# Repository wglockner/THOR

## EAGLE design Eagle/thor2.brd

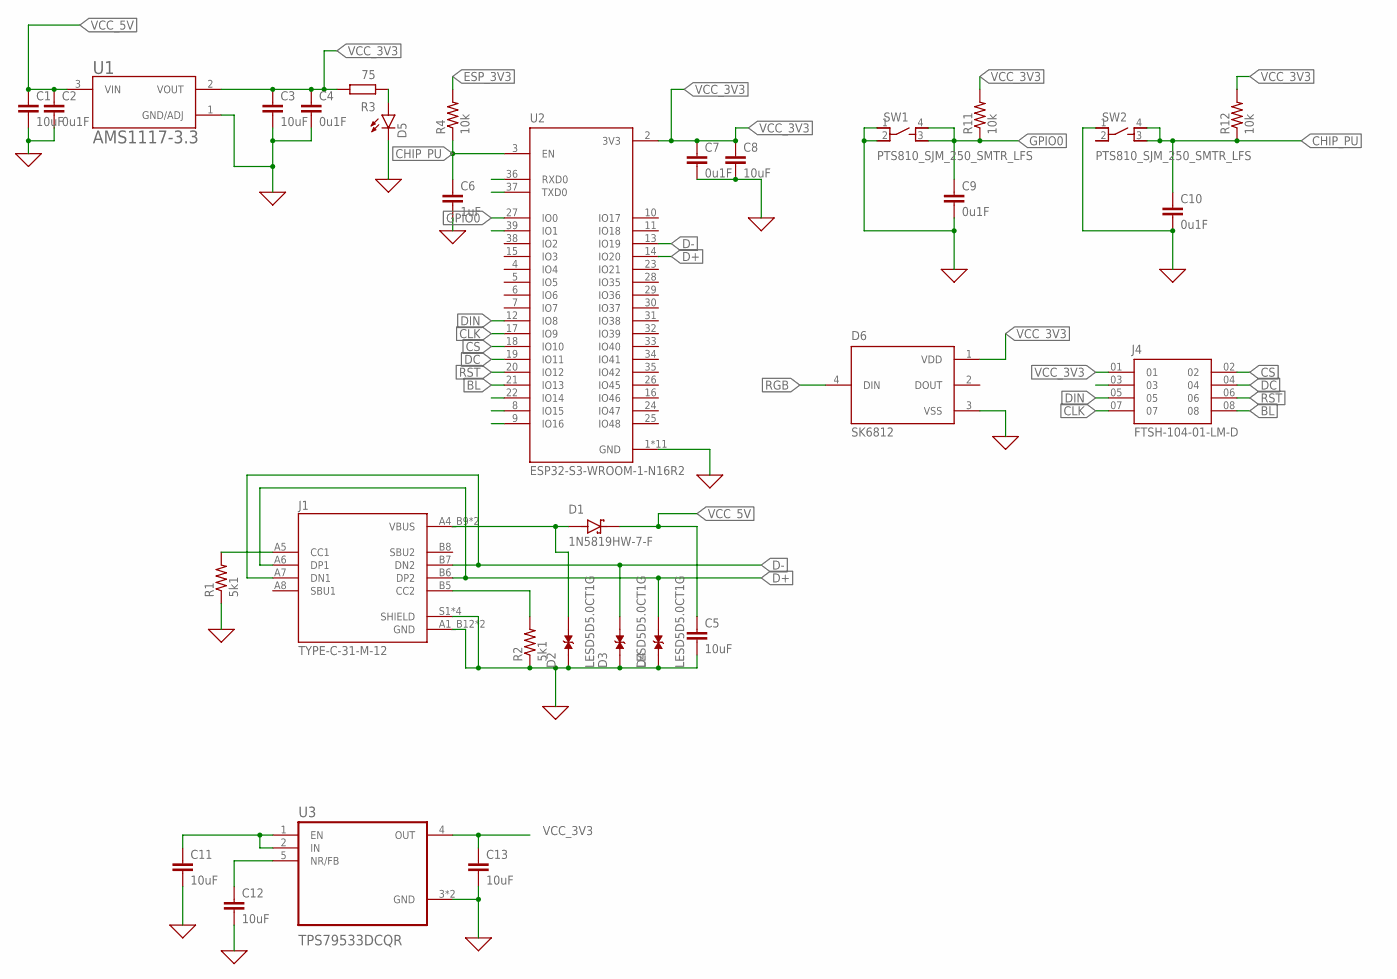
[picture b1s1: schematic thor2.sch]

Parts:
C1, C3, C5, C8, C11, C12, C13: 10uF; C2.5-3
C2, C4, C7, C9, C10: 0u1F; C2.5-3
C6: 1uF; C2.5-3
D1: 1N5819HW-7-F; SOD3715X145N
D2, D3, D4: LESD5D5.0CT1G; TVS_LESD5D5.0CT1G
D5: LED; SMARTLED-TTW
D6: SK6812; LED_SK6812
J1: TYPE-C-31-M-12; HRO_TYPE-C-31-M-12
J4: FTSH-104-01-LM-D; SAMTEC_FTSH-104-01-LM-D
R1, R2: 5k1; R1206
R4, R11, R12: 10k; R1206
SW1, SW2: PTS810_SJM_250_SMTR_LFS; SW_PTS810_SJM_250_SMTR_LFS
U1: AMS1117-3.3; SOT229P700X180-4N
U2: ESP32-S3-WROOM-1-N16R2; XCVR_ESP32-S3-WROOM-1-N16R2
U3: TPS79533DCQR; SOT127P706X180-6N

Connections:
0: C1.2, C2.2, C3.2, C4.2, C5.2, C6.2, C7.2, C8.2, C9.2, C10.2, C11.2, C12.2, C13.2, D2.1, D3.1, D4.1, D5.C@1 (C), D6.3 (VSS), J1.A1_B12 (GND), J1.B1_A12 (GND), J1.S1 (SHIELD), J1.S2 (SHIELD), J1.S3 (SHIELD), J1.S4 (SHIELD), R1.1, R2.1, SW1.1, SW1.2, SW2.1, U1.1 (GND/ADJ), U2.1 (GND), U2.40 (GND), U2.41_1 (GND), U2.41_2 (GND), U2.41_3 (GND), U2.41_4 (GND), U2.41_5 (GND), U2.41_6 (GND), U2.41_7 (GND), U2.41_8 (GND), U2.41_9 (GND), U3.3 (GND), U3.6 (GND)
BL: J4.08, U2.21 (IO13)
CHIP_PU: C6.1, C10.1, R4.1, R12.1, SW2.3, SW2.4, U2.3 (EN)
CLK: J4.07, U2.17 (IO9)
CS: J4.02, U2.18 (IO10)
D+: D4.2, J1.A6 (DP1), J1.B6 (DP2), U2.14 (IO20)
D-: D3.2, J1.A7 (DN1), J1.B7 (DN2), U2.13 (IO19)
DC: J4.04, U2.19 (IO11)
DIN: J4.05, U2.12 (IO8)
ESP_3V3: R4.2
GPIO0: C9.1, R11.1, SW1.3, SW1.4, U2.27 (IO0)
unnamed: C11.1, U3.1 (EN), U3.2 (IN)
unnamed: J1.A5 (CC1), R1.2
unnamed: J1.B5 (CC2), R2.2
unnamed: D1.A, D2.2, J1.A4_B9 (VBUS), J1.B4_A9 (VBUS)
unnamed: C12.1, U3.5 (NR/FB)
RGB: D6.4 (DIN)
RST: J4.06, U2.20 (IO12)
VCC_3V3: C3.1, C4.1, C7.1, C8.1, C13.1, D6.1 (VDD), J4.01, R11.2, R12.2, U1.2 (VOUT), U2.2 (3V3), U3.4 (OUT)
VCC_5V: C1.1, C2.1, C5.1, D1.C (K), U1.3 (VIN)

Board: 2 copper layers, 31 parts (0 on the bottom side), 18 nets, no tracks yet.

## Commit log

2024-10-09 initial_commit
